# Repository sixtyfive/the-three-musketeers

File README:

I needed something to feed three audio sources into my amplifier's AUX input.
I also wanted to learn how to design a simple schematic and PCB with Eagle.

That's it.

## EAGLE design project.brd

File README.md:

I needed something to feed three audio sources into my amplifier's AUX input. I also wanted to learn how to design a simple schematic and PCB with Eagle. As a power source I wanted to be able to use any USB port, so the power supply schematic turned out more complex than the actual thing.

Anyways, that's it.

Careful with the PCB, the current version hasn't been made yet.

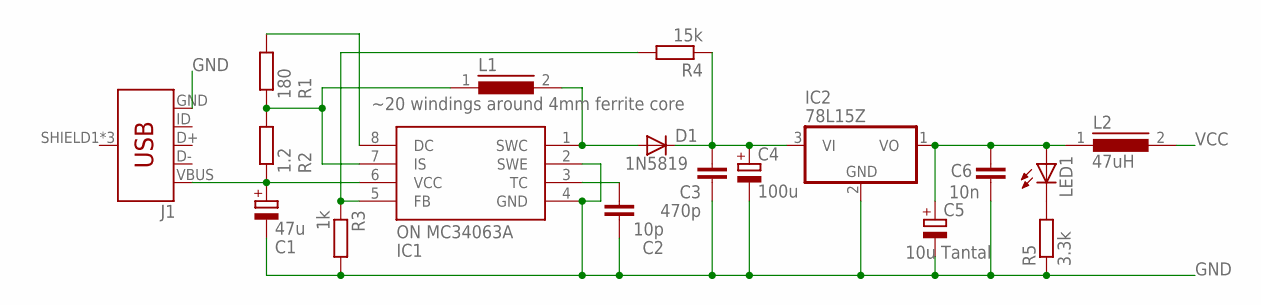
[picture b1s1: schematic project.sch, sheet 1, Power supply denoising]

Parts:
C1: 47u; E2,5-5
C2: 10p; C050-024X044
C3: 470p; C050-024X044
C4: 100u; E2,5-5
C5: 10u Tantal; E2-4
C6: 10n; C050-024X044
D1: 1N5819; DO41-10
IC1: ON MC34063A; DIL08
IC2: 78L15Z; TO92
J1: USB_MICRO-B_FEMALE-SMT; USB-B-MICRO-SMD
L1: ~20 windings around 4mm ferrite core; 82114R
L2: 47uH; MCC10
LED1: LED5MM
R1: 180; 0207/7
R2: 1.2; 0207/7
R3: 1k; 0207/7
R4: 15k; 0207/7
R5: 3.3k; 0207/7

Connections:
GND: C1.-, C2.1, C3.1, C4.-, C5.-, C6.1, IC1.2 (SWE), IC1.4 (GND), IC2.2 (GND), R3.2, R5.1; also elsewhere on the board
unnamed: IC1.8 (DC), R1.2
unnamed: D1.A, IC1.1 (SWC), L1.2
unnamed: C5.+, C6.2, IC2.1 (VO), L2.1, LED1.A
unnamed: C3.2, C4.+, D1.C, IC2.3 (VI), R4.1
unnamed: LED1.K (C), R5.2
unnamed: C2.2, IC1.3 (TC)
unnamed: IC1.5 (FB), R3.1, R4.2
unnamed: C1.+, IC1.6 (VCC), J1.VBUS, R2.1
unnamed: IC1.7 (IS), L1.1, R1.1, R2.2
VCC: L2.2; also elsewhere on the board

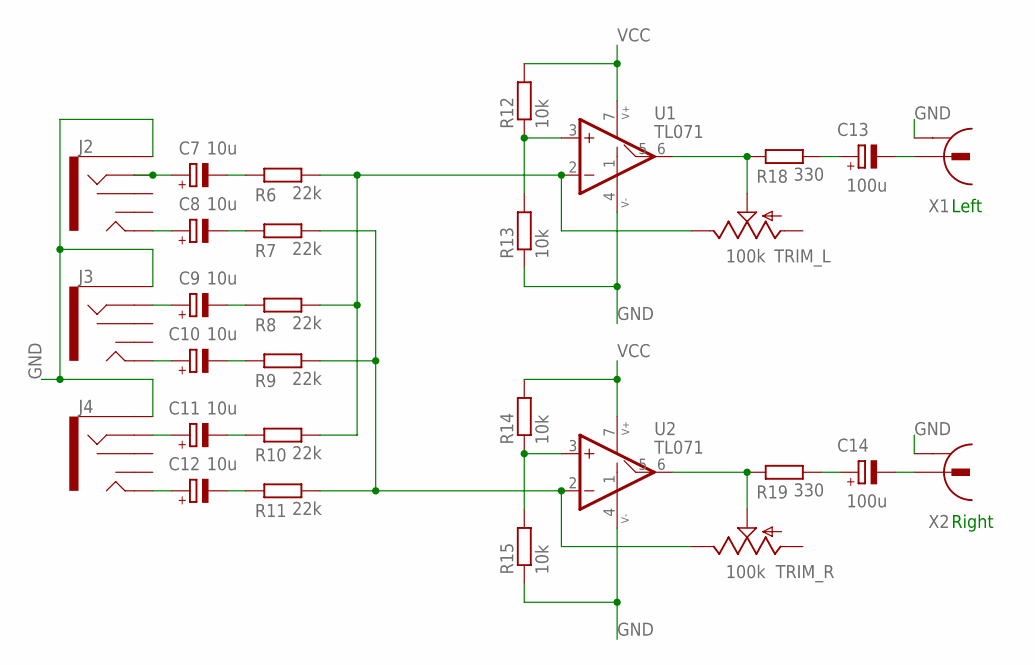
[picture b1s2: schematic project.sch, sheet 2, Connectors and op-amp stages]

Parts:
C7, C8, C9, C10, C11, C12: 10u; E2-4
C13, C14: 100u; E2-4
J2, J3, J4: AUDIO_JACK_3.5MM_KIT; AUDIO-JACK-KIT
R6, R7, R8, R9, R10, R11: 22k; 0204/5
R12, R13, R14, R15: 10k; 0204/5
R18, R19: 330; 0204/5
TRIM_L: 100k; B25P
TRIM_R: 100k; B25P
U1, U2: TL071; DIL08
X1, X2: CONRAD_736880-49; CINCH

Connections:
GND: J2.SLEEVE, J3.SLEEVE, J4.SLEEVE, R13.1, R15.1, U1.4 (V-), U2.4 (V-), X1.2, X2.2; also elsewhere on the board
unnamed: C13.-, X1.1
unnamed: C13.+, R18.2
unnamed: C14.-, X2.1
unnamed: C7.-, R6.1
unnamed: R18.1, TRIM_L.S, U1.6 (OUT)
unnamed: C14.+, R19.2
unnamed: C7.+, J2.RING
unnamed: R12.1, R13.2, U1.3 (+IN)
unnamed: C8.+, J2.TIP
unnamed: R6.2, R8.2, R10.2, TRIM_L.E, U1.2 (-IN)
unnamed: C8.-, R7.1
unnamed: C9.+, J3.RING
unnamed: C9.-, R8.1
unnamed: C10.+, J3.TIP
unnamed: C10.-, R9.1
unnamed: C11.+, J4.RING
unnamed: C11.-, R10.1
unnamed: C12.+, J4.TIP
unnamed: C12.-, R11.1
unnamed: R19.1, TRIM_R.S, U2.6 (OUT)
unnamed: R14.1, R15.2, U2.3 (+IN)
unnamed: R7.2, R9.2, R11.2, TRIM_R.E, U2.2 (-IN)
VCC: R12.2, R14.2, U1.7 (V+), U2.7 (V+); also elsewhere on the board

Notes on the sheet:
Left
Right

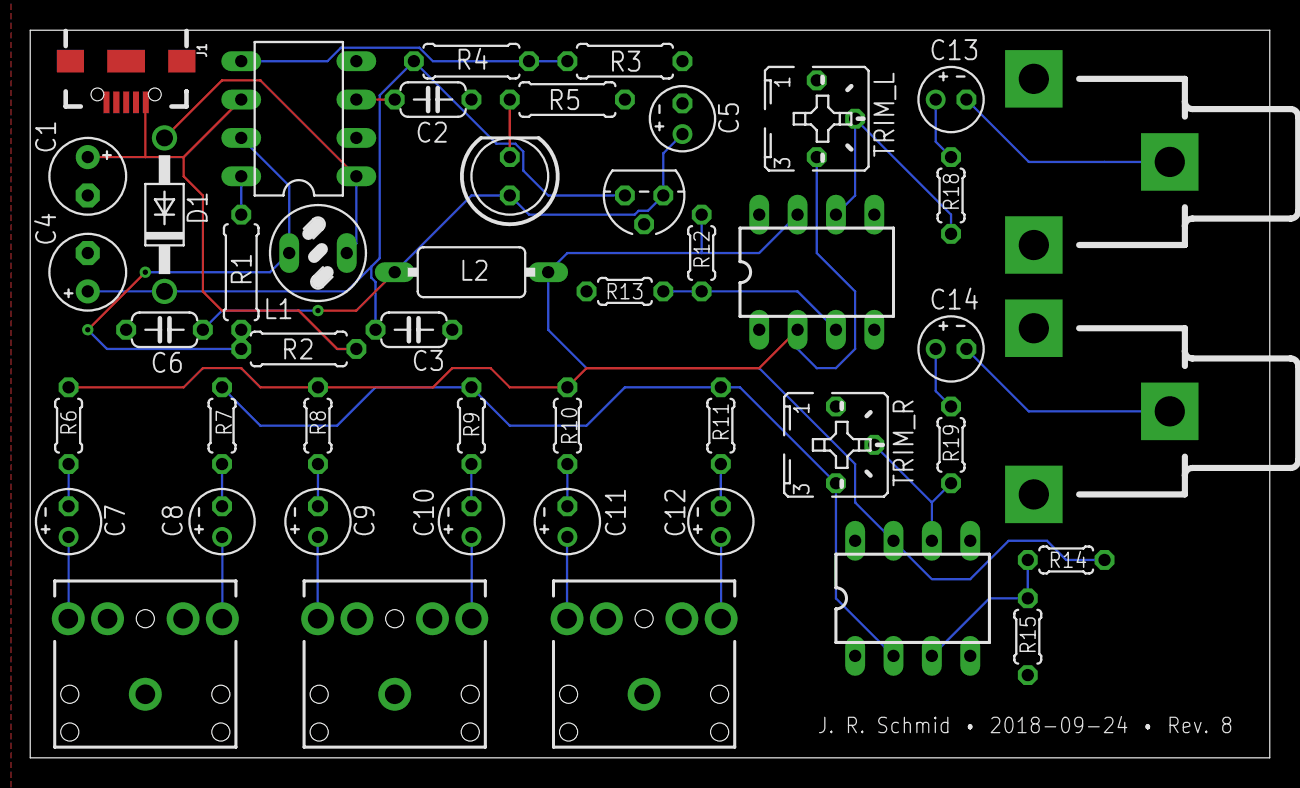
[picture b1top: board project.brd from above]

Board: 2 copper layers, 82.1 x 48.2 mm, 47 parts (0 on the bottom side), 33 nets.

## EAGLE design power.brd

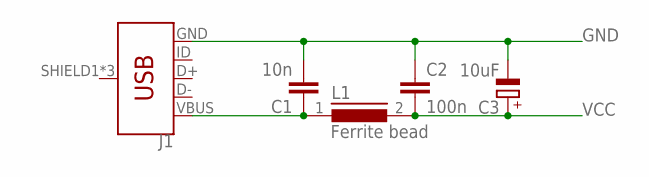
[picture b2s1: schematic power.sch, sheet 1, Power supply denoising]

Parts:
C1: 10n; C050-024X044
C2: 100n; C050-024X044
C3: 10uF; E2,5-5
J1: USB_MICRO-B_FEMALE-SMT; USB-B-MICRO-SMD
L1: Ferrite bead; MMICC7

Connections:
GND: C1.2, C2.1, C3.-, J1.GND; also elsewhere on the board
VBUS: C1.1, J1.VBUS, L1.1
VCC: C2.2, C3.+, L1.2; also elsewhere on the board

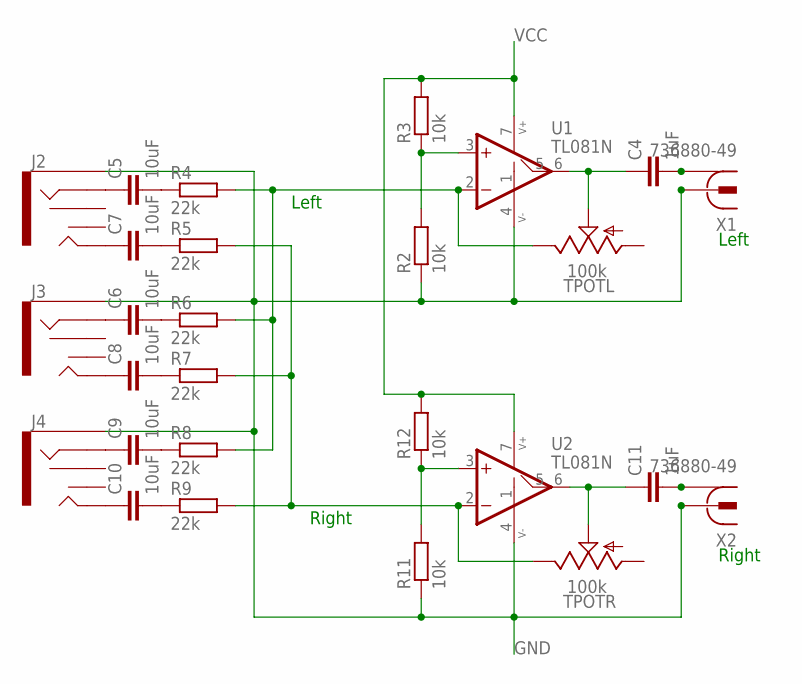
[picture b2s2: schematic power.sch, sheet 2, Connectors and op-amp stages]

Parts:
C4, C11: 1uF; C050-024X044
C5, C6, C7, C8, C9, C10: 10uF; C050-024X044
J2, J3, J4: AUDIO_JACK_3.5MM_KIT; AUDIO-JACK-KIT
R2, R3, R11, R12: 10k; 0204/5
R4, R5, R6, R7, R8, R9: 22k; 0204/5
TPOTL: 100k; B25P
TPOTR: 100k; B25P
U1, U2: TL081N; DIL08
X1, X2: 736880-49

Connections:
GND: J2.SLEEVE, J3.SLEEVE, J4.SLEEVE, R2.1, R11.1, U1.4 (V-), U2.4 (V-), X1.2, X2.2; also elsewhere on the board
unnamed: R4.2, R6.2, R8.2, TPOTL.E, U1.2 (-IN)
unnamed: C4.1, TPOTL.S, U1.6 (OUT)
unnamed: C4.2, X1.1, X1.1@1 (1), X1.1@2 (1)
unnamed: C5.1, J2.RING
unnamed: R2.2, R3.1, U1.3 (+IN)
unnamed: C6.1, J3.RING
unnamed: C7.1, J2.TIP
unnamed: C8.1, J3.TIP
unnamed: C9.1, J4.RING
unnamed: C10.1, J4.TIP
unnamed: C5.2, R4.1
unnamed: C7.2, R5.1
unnamed: C6.2, R6.1
unnamed: C8.2, R7.1
unnamed: C9.2, R8.1
unnamed: C10.2, R9.1
unnamed: C11.1, TPOTR.S, U2.6 (OUT)
unnamed: C11.2, X2.1, X2.1@1 (1), X2.1@2 (1)
unnamed: R11.2, R12.1, U2.3 (+IN)
unnamed: R5.2, R7.2, R9.2, TPOTR.E, U2.2 (-IN)
VCC: R3.2, R12.2, U1.7 (V+), U2.7 (V+); also elsewhere on the board

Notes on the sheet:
Left
Right

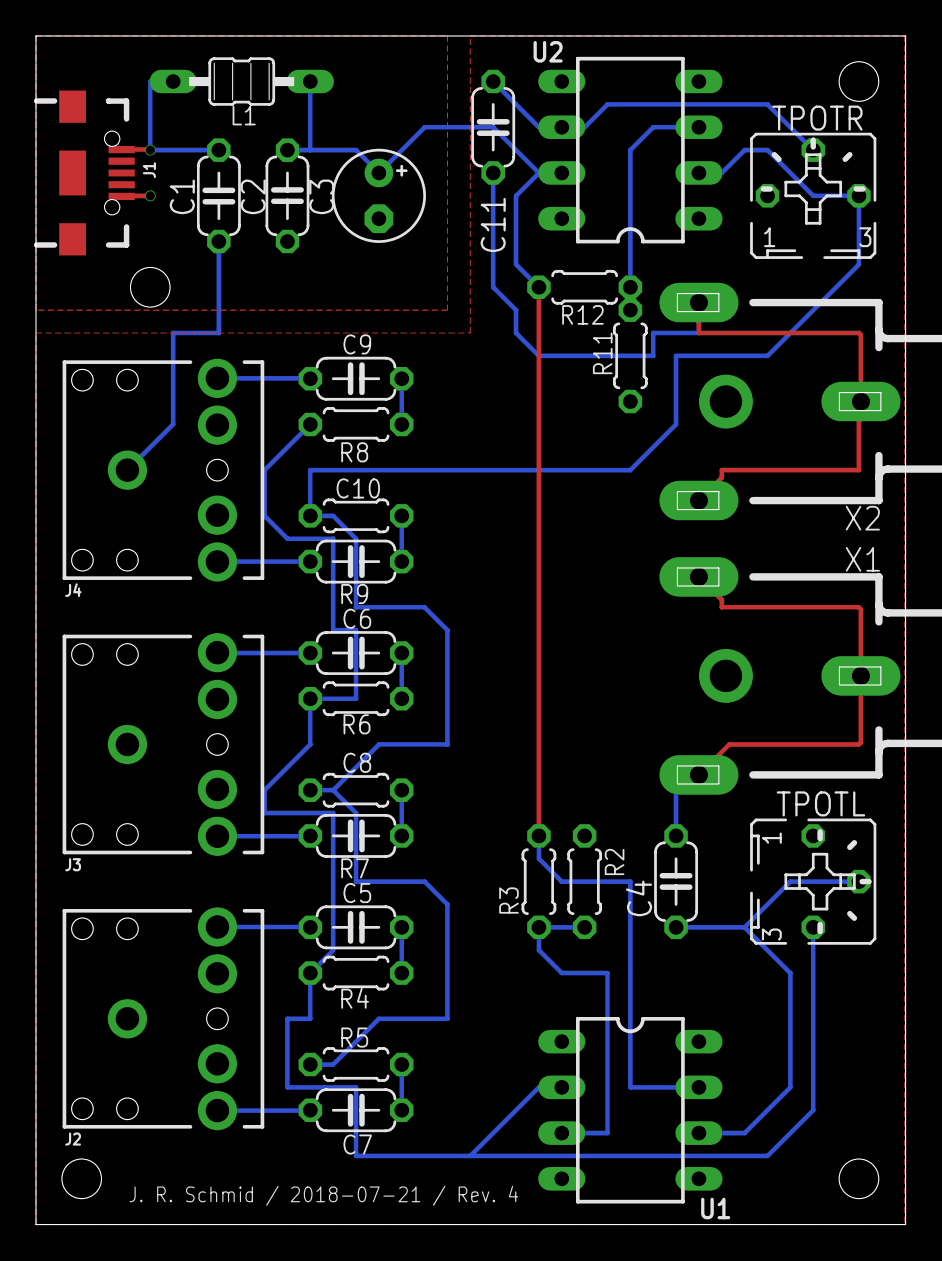
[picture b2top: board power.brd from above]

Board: 2 copper layers, 48.3 x 66.0 mm, 32 parts (0 on the bottom side), 23 nets.

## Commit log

2018-07-21 Initial import: schema and board.
2018-07-21 Moving bDocu contents slightly
2018-07-21 Adding Gerber rules
2018-07-21 Ignore Gerber files.
2018-07-21 Adding Aisler DRC.
2018-07-21 Moving labels to (t,b)Place
2018-07-21 Updating Rev label
2018-07-21 Bugfix
2018-07-21 Removing unneeded info from schematic
2018-07-21 Adding screenshots
2018-07-21 Adding LICENSE and README to be able to upload project to GitHub
2018-07-21 Linking to screenshots
2018-07-21 Renaming to match type
2018-07-21 Renaming to be replaced
2018-07-21 Replacing with official file
2018-07-21 Cleaning up part designation locations
2018-07-21 Adding Makefile, for cleaning up only so far
2018-07-21 Renaming to something generic
2018-07-21 Minor positioning adjustments
2018-07-21 Bumping revision
2018-07-21 Updating screenshots
2018-07-22 Moving things around
2018-08-13 Fixing all bugs thus far that were in the schematic. PCB layout now broken!
2018-09-22 Updating with new power supply Rev.
2018-09-22 Updating README
2018-09-23 Updating to latest prototype revision.
2018-09-23 Updating from latest schematic.
2018-09-23 Adding warning to README.
2018-09-23 Re-doing the PCB.
2018-09-23 Nicer image.
2018-09-23 GitHub not getting the change...
2018-09-23 Re-uploading...
2019-10-05 Adding results for first round of research.
2019-10-05 Wait, one more!
2019-10-05 Adding AGC circuits

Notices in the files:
parts and their libraries:
SparkFun-Connectors: Licensing: Creative Commons ShareAlike 4.0 International - https://creativecommons.org/licenses/by-sa/4.0
op-amp: Copyright (C) 2006 by Bob Starr
